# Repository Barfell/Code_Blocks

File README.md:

# Code Blocks
Code Blocks &amp; Examples for Projects

Contains example code and projects for various platforms (mainly embedded).

## Procedure to setup Git on the PC (SSH):

1. Generate and add SSH keys (https://help.github.com/enterprise/2.3/user/articles/generating-an-ssh-key/)

2. Clone the Git repository

    ```
    git clone <your_repository_url>
    ```

## Work flow

1. Start playing with your git tools as soon as possible. Here is a [cheat sheet](https://training.github.com/kit/downloads/github-git-cheat-sheet.pdf) with the most important commands. The basic commands for committing your changes are:
    ```
    git add <file_or_folder> # git add -A in case there are new unversioned files
    git commit -m "commit message" 
    git push origin <your_branch> 
    ```

2. When committing your work, it is important to tag each commit with a meaningful message, so that all contributors understand what changes have been made and it is easier to roll-back to earlier revisions in case a mistake has been made. Here is a guide on [how to write better commit messages](https://robots.thoughtbot.com/5-useful-tips-for-a-better-commit-message), so that your repository doesn't end up [like this](https://xkcd.com/1296/).

3. Make use of the [`.gitignore`](http://git-scm.com/docs/gitignore) file. You should never commit intermediate or generated files. The repository should contain only source code and build/automation scripts.

4. Make a habit of branching your work whenever you implement or experiment with new features. Apart from that, each developer in a group should work on her/his own separate branch on different work sets. The `master` branch should contain _final_ or _working_ features. Refer to [this document](https://git-scm.com/book/en/v2/Git-Branching-Basic-Branching-and-Merging) for an overview on the basic principles of branching and merging. 

## Issues & Contributions

Any bug, feature or problem can be managed within a lab group using [the issue tracker](https://guides.github.com/features/issues/). We recommend using it freely on the local repository as means to manage work packages and communicate problems.

If you identify a problem of general interest or related to the provided material you can open an issue on the main (public) repository, which will be visible to all developers. Please take your time and be mindful of what you post in the public domain since it is _really important_ that the issue is correct, concise, and is accompanied by a short description of context in which the issue arose. [Here](https://wiredcraft.com/blog/how-we-write-our-github-issues/) and [here](https://upthemes.com/blog/2014/02/writing-useful-github-issues/) are two discussions in how to write meaningful issues. An issue can be confirmed or invalidated, depending on whether or not it is reproducible.

If you know how to solve an opened issue and would like to contribute to the development of the software, feel free to [fork](https://help.github.com/enterprise/2.4/user/articles/fork-a-repo/) the main repository and [issue a pull request](https://help.github.com/articles/using-pull-requests/) when you believe you have solved the problem. The solution will be evaluated and if valid, will be merged into the `master` branch.

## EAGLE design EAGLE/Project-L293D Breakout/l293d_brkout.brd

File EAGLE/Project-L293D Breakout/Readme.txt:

Breakout board for L293 motor controller.

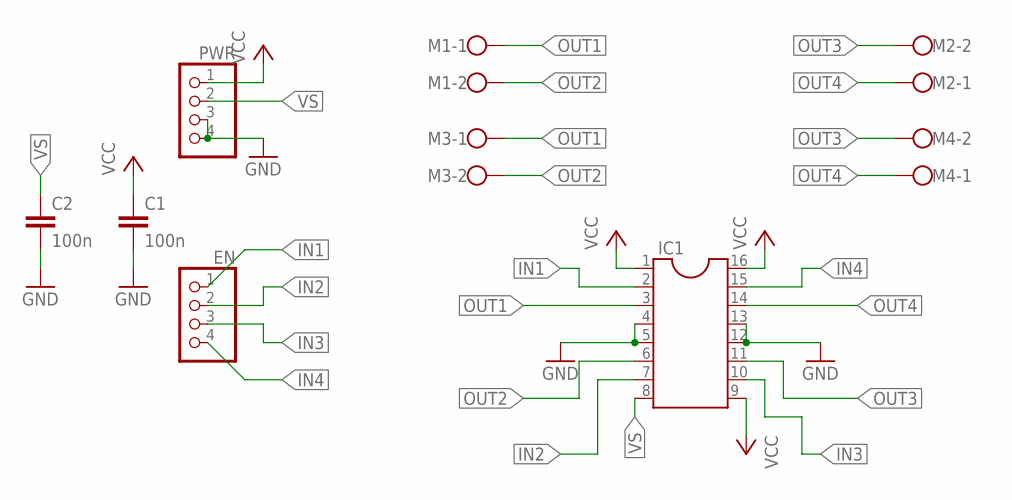
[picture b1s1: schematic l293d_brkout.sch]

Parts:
C1, C2: 100n; C2.5-2
EN: PINHD-1X4; 1X04
IC1: DIL16S; SOCKET-16
M1, M2, M3, M4: W237-102
PWR: PINHD-1X4; 1X04

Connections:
GND: C1.2, C2.2, IC1.4, IC1.5, IC1.12, IC1.13, PWR.3, PWR.4
IN1: EN.1, IC1.2
IN2: EN.2, IC1.7
IN3: EN.3, IC1.10
IN4: EN.4, IC1.15
OUT1: IC1.3, M1.1, M3.1
OUT2: IC1.6, M1.2, M3.2
OUT3: IC1.11, M2.2, M4.2
OUT4: IC1.14, M2.1, M4.1
VCC: C1.1, IC1.1, IC1.9, IC1.16, PWR.1
VS: C2.1, IC1.8, PWR.2

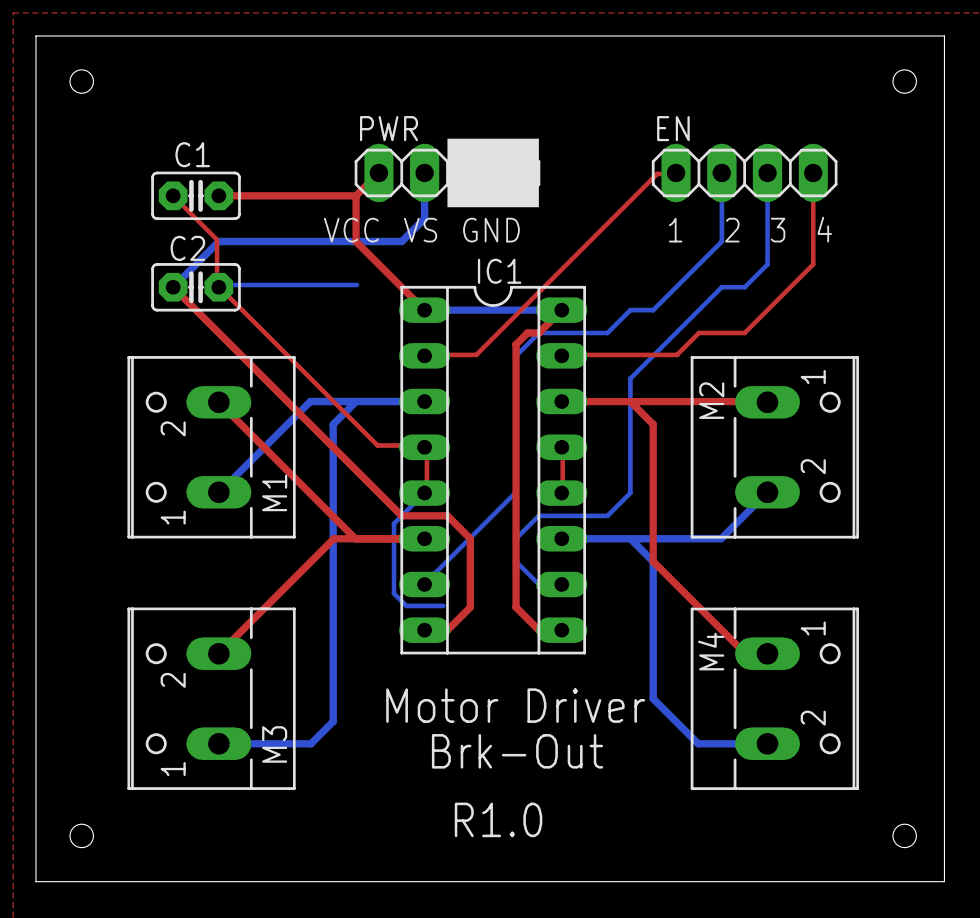
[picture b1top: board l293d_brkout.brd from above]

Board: 2 copper layers, 50.5 x 47.0 mm, 9 parts (0 on the bottom side), 11 nets.

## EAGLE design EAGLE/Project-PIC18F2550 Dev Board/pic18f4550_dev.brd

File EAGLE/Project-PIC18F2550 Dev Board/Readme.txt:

Development board for PIC18F2550 MCU (28-pin PDIP).

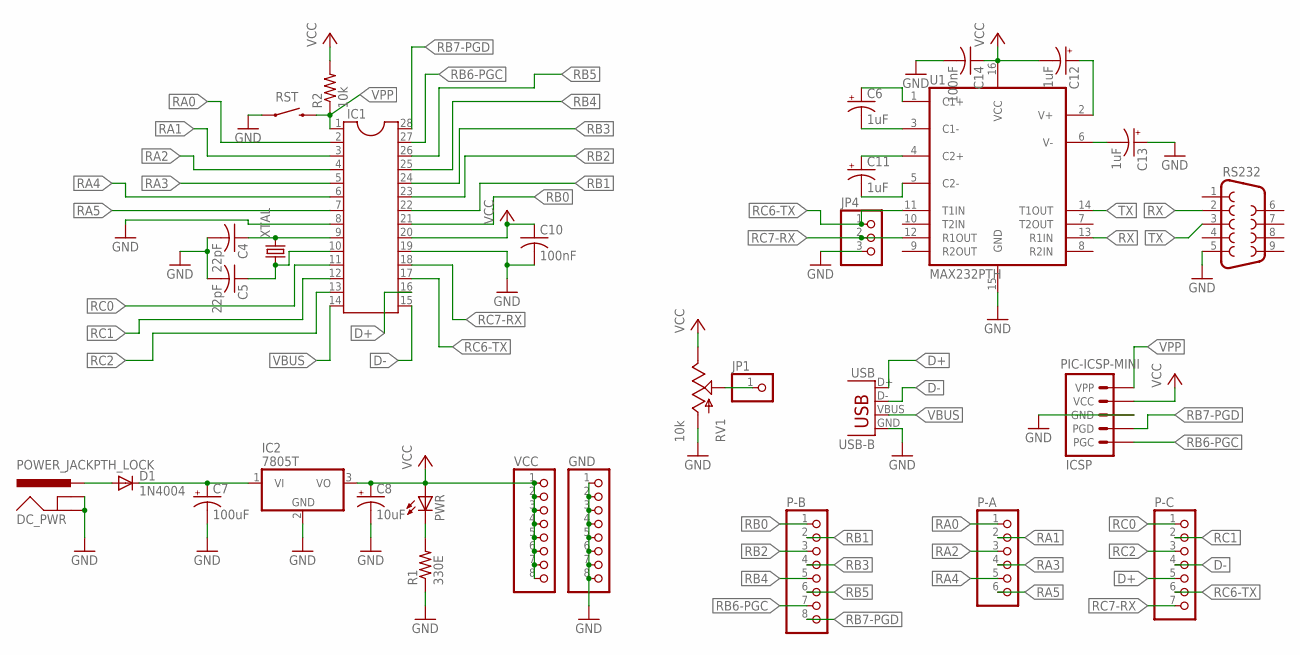
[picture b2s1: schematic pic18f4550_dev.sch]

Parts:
C4, C5: 22pF; C025-024X044
C6, C11, C12, C13: 1uF; CPOL-RADIAL-10UF-25V
C7: 100uF; CPOL-RADIAL-100UF-25V
C8: 10uF; CPOL-RADIAL-10UF-25V
C10, C14: 100nF; C025-025X050
D1: 1N4004; DO41-10
DC_PWR: POWER_JACKPTH_LOCK; POWER_JACK_PTH_LOCK
GND: PINHD-1X8; 1X08
IC1: DIL28-3
IC2: 7805T; TO220H
ICSP: PIC-ICSP-MINI
JP1: PINHD-1X1; 1X01
JP4: PINHD-1X3; 1X03
P-A: PINHD-1X6; 1X06
P-B: PINHD-1X8; 1X08
P-C: PINHD-1X7; 1X07
PWR: LED5MM
R1: 330E; 0204/7
R2: 10k; 0204/7
RS232: DB9FEMALE; DB9
RST: SWITCH-MOMENTARY-2PTH; TACTILE-PTH
RV1: 10k; TRIM_POT
U1: MAX232PTH; DIL16
USB: USB-B; USB-B-PTH
VCC: PINHD-1X8; 1X08
XTAL: CRYSTALHC49S; HC49/S

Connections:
D+: IC1.16, P-C.5, USB.D+
D-: IC1.15, P-C.4, USB.D-
GND: C4.2, C5.2, C7.2 (-), C8.2 (-), C10.2, C13.1 (+), C14.2, DC_PWR.GND, DC_PWR.GNDBREAK, GND.1, GND.2, GND.3, GND.4, GND.5, GND.6, GND.7, GND.8, IC1.8, IC1.19, IC2.2 (GND), ICSP.3 (GND), JP4.3, R1.1, RS232.5, RST.1, RV1.3 (A), U1.15 (GND), USB.GND
unnamed: C6.1 (+), U1.1 (C1+)
unnamed: C4.1, IC1.9, XTAL.2
unnamed: C5.1, IC1.10, XTAL.1
unnamed: C7.1 (+), D1.C, IC2.1 (VI)
unnamed: C6.2 (-), U1.3 (C1-)
unnamed: C11.1 (+), U1.4 (C2+)
unnamed: C11.2 (-), U1.5 (C2-)
unnamed: C12.1 (+), U1.2 (V+)
unnamed: C13.2 (-), U1.6 (V-)
unnamed: PWR.K (C), R1.2
unnamed: D1.A, DC_PWR.PWR
unnamed: JP1.1, RV1.1 (S)
RA0: IC1.2, P-A.1
RA1: IC1.3, P-A.2
RA2: IC1.4, P-A.3
RA3: IC1.5, P-A.4
RA4: IC1.6, P-A.5
RA5: IC1.7, P-A.6
RB0: IC1.21, P-B.1
RB1: IC1.22, P-B.2
RB2: IC1.23, P-B.3
RB3: IC1.24, P-B.4
RB4: IC1.25, P-B.5
RB5: IC1.26, P-B.6
RB6-PGC: IC1.27, ICSP.5 (PGC), P-B.7
RB7-PGD: IC1.28, ICSP.4 (PGD), P-B.8
RC0: IC1.11, P-C.1
RC1: IC1.12, P-C.2
RC2: IC1.13, P-C.3
RC6-TX: IC1.17, JP4.1, P-C.6, U1.11 (T1IN)
RC7-RX: IC1.18, JP4.2, P-C.7, U1.12 (R1OUT)
RX: RS232.2, U1.13 (R1IN)
TX: RS232.3, U1.14 (T1OUT)
VBUS: IC1.14, USB.VBUS
VCC: C8.1 (+), C10.1, C12.2 (-), C14.1, IC1.20, IC2.3 (VO), ICSP.2 (VCC), PWR.A, R2.2, RV1.2 (E), U1.16 (VCC), VCC.1, VCC.2, VCC.3, VCC.4, VCC.5, VCC.6, VCC.7, VCC.8
VPP: IC1.1, ICSP.1 (VPP), R2.1, RST.3 (2)

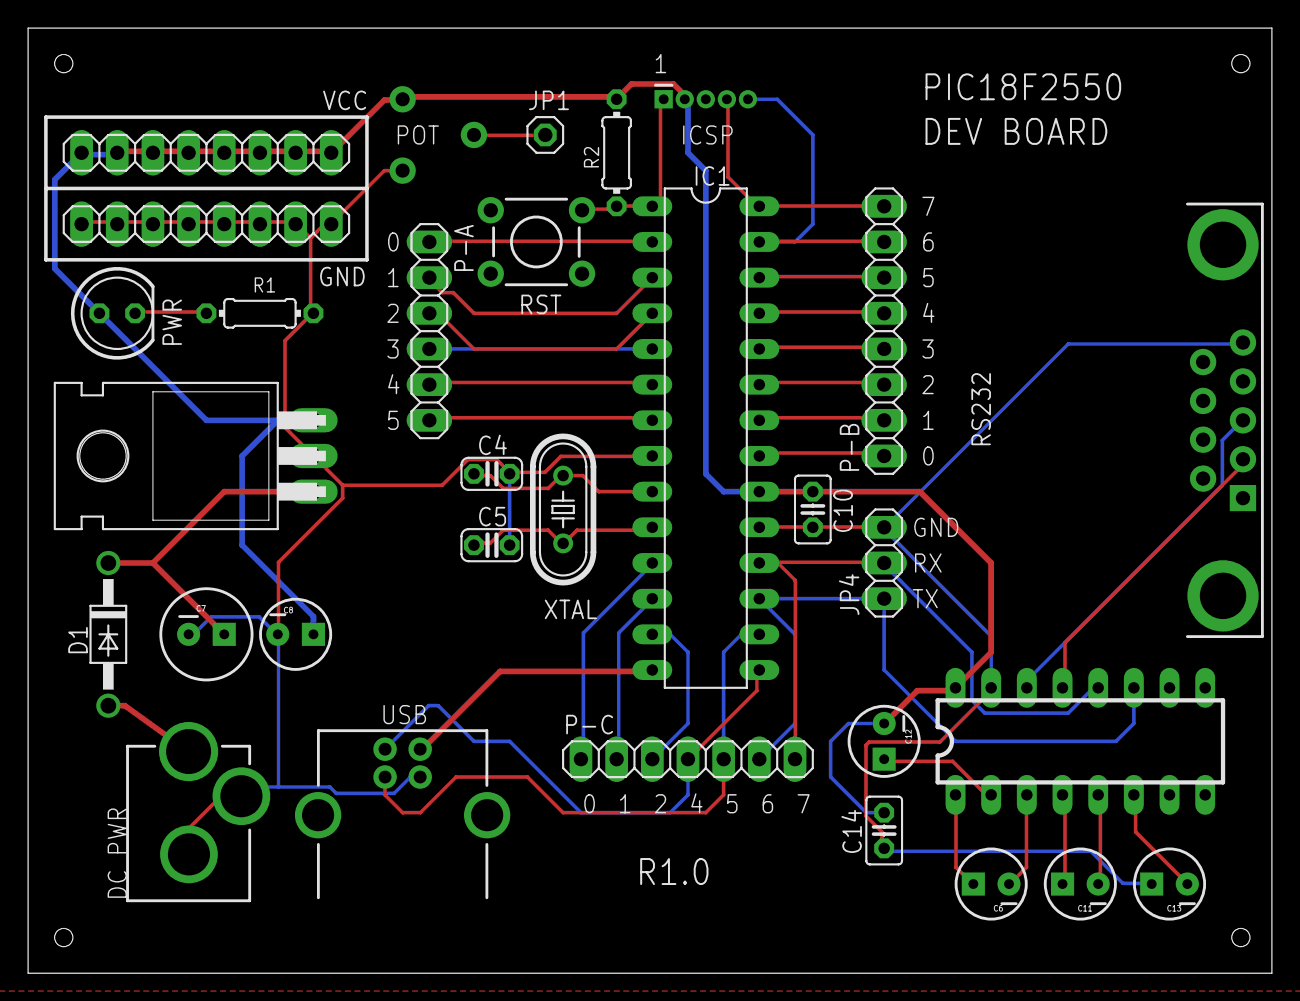
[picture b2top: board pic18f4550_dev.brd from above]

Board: 2 copper layers, 88.6 x 67.3 mm, 31 parts (0 on the bottom side), 39 nets.

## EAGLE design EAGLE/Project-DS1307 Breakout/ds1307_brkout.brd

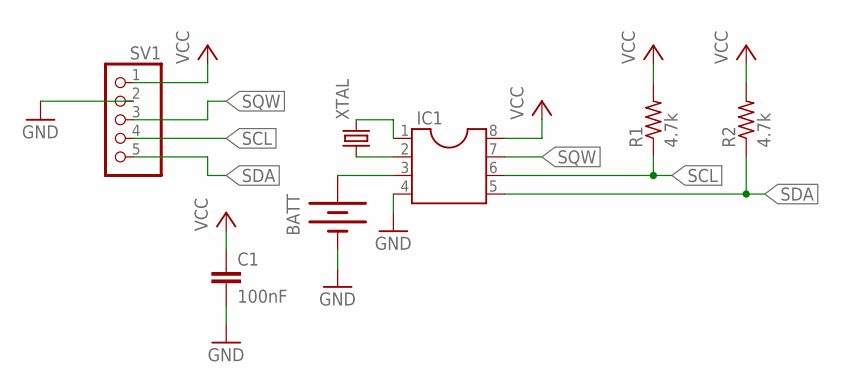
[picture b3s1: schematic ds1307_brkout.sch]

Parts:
BATT: BATTERY20PTH; BATTCOM_20MM_PTH
C1: 100nF; C2.5-5
IC1: DIL8S; SOCKET-08
R1, R2: 4.7k; 0207/12
SV1: PINHD-1X5; 1X05
XTAL: CRYSTALTC26H; TC26H

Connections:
GND: BATT.2 (-), C1.2, IC1.4, SV1.2
unnamed: IC1.1, XTAL.2
unnamed: IC1.2, XTAL.1
unnamed: BATT.1 (+), IC1.3
SCL: IC1.6, R1.1, SV1.4
SDA: IC1.5, R2.1, SV1.5
SQW: IC1.7, SV1.3
VCC: C1.1, IC1.8, R1.2, R2.2, SV1.1

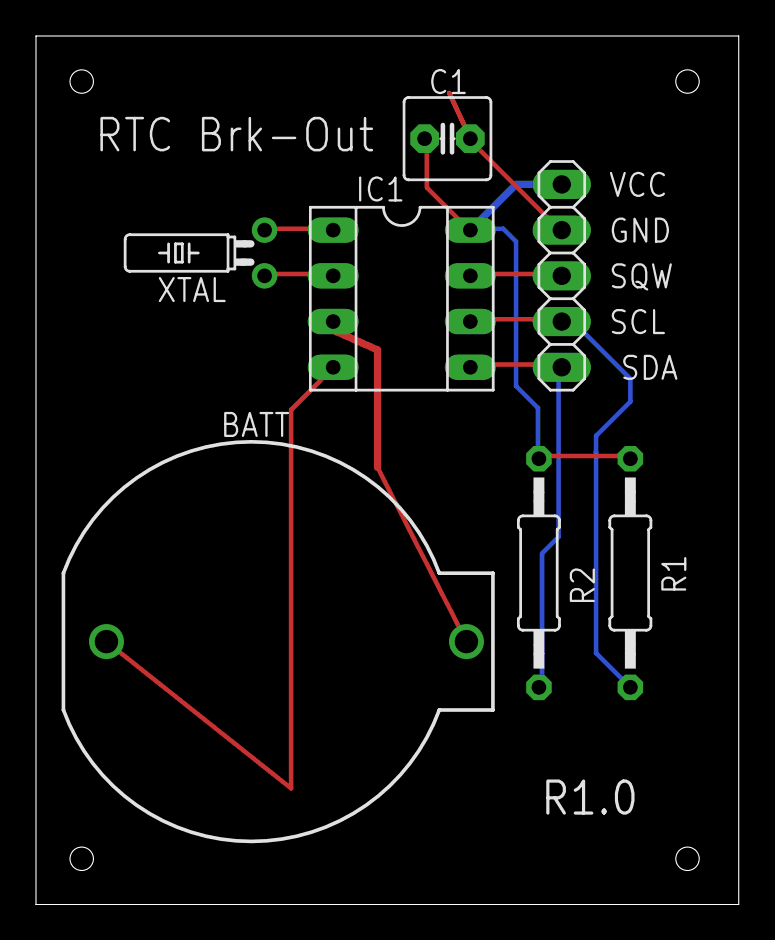
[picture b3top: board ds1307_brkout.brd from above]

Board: 2 copper layers, 39.0 x 48.2 mm, 7 parts (0 on the bottom side), 8 nets.

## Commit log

2016-03-12 "First Commit"
2016-03-12 Modified README.md
2016-03-19 Added Projects
2016-03-19 Added documentation for Ada and Nios-2 code blocks and for Cruise Control Project
2016-03-27 Device Driver Hello World
2016-03-27 Added Readme
2016-03-27 Rearranged files
2016-03-27 Updated Makefile
2016-03-27 Cleaned up the directories
2016-03-28 Added __init & __exit, moved MODULE_ lines to end of code
2016-03-30 Updated readme, added template for a basic char driver module and a corresponding userspace program
2016-03-30 Cleaned directory
2016-03-30 cleaned directories
2016-03-31 Add Memory_Based_Char_Driver Example
2016-03-31 Cleaning
2016-04-02 GPIO Example code in C for RPi
2016-04-02 Rearranged Python source files for RPi
2016-06-08 Updated Repo
2016-07-17 Added STM32Cube project for SW4STM32, updated Led blink code, added PWM timer and configured RTC to use internal oscillator
2016-07-19 Updated STM32L1XX project, add STM32L1XX project for FreeRTOS
2016-07-19 Updated directory structure, interrupt use as per STM HAL guidelines
2016-07-19 Updated timer polling code as per new project structure
2016-07-19 Updated timer PWM code as per new project structure
2016-07-19 Added FreeRTOS example project for STM32L1XX_Discovery
2016-07-20 Updated UART code as per new project structure, add program to use UART with interrupts
2016-07-20 Added debug printf()
2016-07-20 Updated STM32 Readme
2016-07-21 Added debug printf() to STM32 FreeRTOS project
2016-07-21 Added STM32 project for UART communication using DMA
2016-07-21 Added debug printf() to STM32 UART DMA project
2016-07-21 Optimised code in STM32 UART DMA project
2016-07-22 Added STM32L476G Discovery basic project
2016-07-23 Added joystick read code to STM32L476G Discovery basic project
2016-07-25 Added USB MSC project for STM32L476G Discovery
2016-07-25 Added debug printf() to USB MSC project for STM32L476G Discovery
2016-07-27 Added Readme to STM32L476G_Discovery_USB_MSC project. Added STM32L476G_Discovery_USB_CDC project.
2016-07-28 Added STM32L476G Discovery LCD project
2016-07-28 Project setting changes
2016-07-29 Disabled USB OTG Power Switch to allow VBUS polling to detect USB connection/disconnection with host
2016-07-29 Added STM32L476G Discovery USB MSC FAT project
2016-07-29 Added FreeRTOS API support to measure stack usage in STM32L476G Discovery USB MSC FAT project
2016-07-30 Added STM32L476G Discovery SAI project
2016-08-02 Added STM32L476G Discovery HID project
2016-08-02 Added click functionality
2016-11-09 Added source code for network socket programming

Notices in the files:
parts and their libraries:
SparkFun-Electromechanical: Licensing: Creative Commons ShareAlike 4.0 International - https://creativecommons.org/licenses/by-sa/4.0
